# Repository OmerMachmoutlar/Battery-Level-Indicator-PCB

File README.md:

# 12V Akü Seviye Göstergesi Tasarımı (PCB Projesi)

Bu proje, harici bir voltaj kaynağını (12V Akü) izlemek için tasarlanmış, baştan sona (tasarım-üretim-montaj) tarafımdan gerçekleştirilmiş bir PCB projesidir.

## Proje Amacı
Akü voltaj seviyesini görsel olarak (LED'ler vb. ile) kullanıcıya bildiren kompakt bir elektronik devre kartı üretmek.

## Kullanılan Teknolojiler ve Süreçler
* **PCB Tasarımı:** Autodesk Eagle (Şematik ve Board çizimi)
* **Üretim Yöntemi:** CNC Kazıma (CNC Milling)
* **Montaj:** Through-hole bileşenlerin manuel lehimlenmesi (Soldering)

## Dosya İçeriği
* Eagle devre şeması.
* PCB yerleşim planı (Layout).
* CNC ile üretilip lehimlenmiş kartın fotoğrafı.

## Kazanımlar
Bu proje ile PCB tasarım kuralları, yol genişlikleri (trace width), CNC ile prototip üretim ve lehimleme teknikleri konusunda pratik deneyim kazanılmıştır.

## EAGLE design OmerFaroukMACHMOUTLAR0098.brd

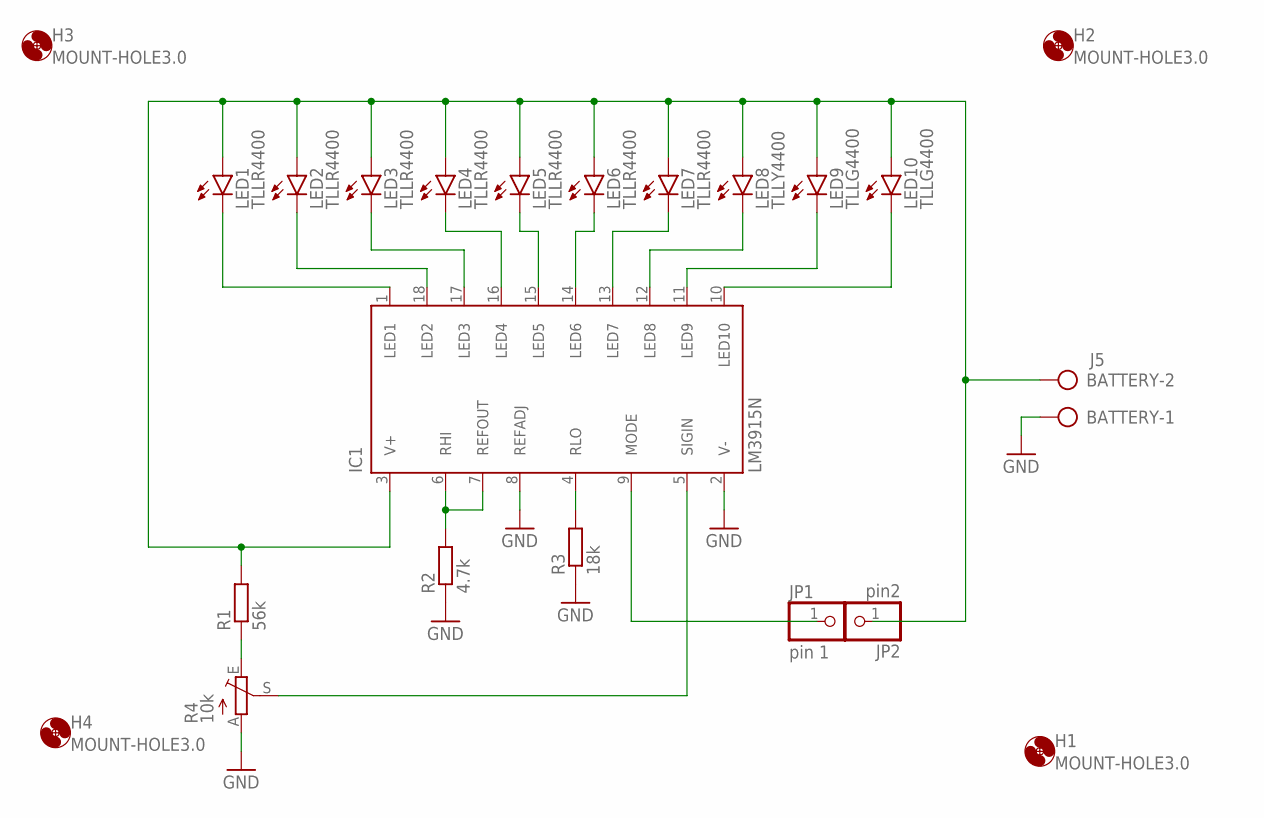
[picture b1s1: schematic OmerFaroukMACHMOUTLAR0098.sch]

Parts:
BATTERY: J5; AK500/2
H1, H2, H3, H4: MOUNT-HOLE3.0; 3,0
IC1: LM3915N; DIL18
JP1: pin 1; 1X01
JP2: pin2; 1X01
LED1, LED2, LED3, LED4, LED5, LED6, LED7: TLLR4400; LED3MM
LED8: TLLY4400; LED3MM
LED9, LED10: TLLG4400; LED3MM
R1: 56k; 0204/7
R2: 4.7k; 0204/7
R3: 18k; 0204/7
R4: 10k; S64W

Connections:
GND: BATTERY.1, IC1.2 (V-), IC1.8 (REFADJ), R2.1, R3.1, R4.A
unnamed: IC1.15 (LED5), LED5.K (C)
unnamed: IC1.14 (LED6), LED6.K (C)
unnamed: IC1.16 (LED4), LED4.K (C)
unnamed: IC1.13 (LED7), LED7.K (C)
unnamed: IC1.17 (LED3), LED3.K (C)
unnamed: IC1.1 (LED1), LED1.K (C)
unnamed: IC1.12 (LED8), LED8.K (C)
unnamed: IC1.18 (LED2), LED2.K (C)
unnamed: IC1.11 (LED9), LED9.K (C)
unnamed: IC1.10 (LED10), LED10.K (C)
unnamed: IC1.6 (RHI), IC1.7 (REFOUT), R2.2
unnamed: IC1.4 (RLO), R3.2
unnamed: BATTERY.2, IC1.3 (V+), JP2.1, LED1.A, LED2.A, LED3.A, LED4.A, LED5.A, LED6.A, LED7.A, LED8.A, LED9.A, LED10.A, R1.2
unnamed: IC1.9 (MODE), JP1.1
unnamed: IC1.5 (SIGIN), R4.S
unnamed: R1.1, R4.E

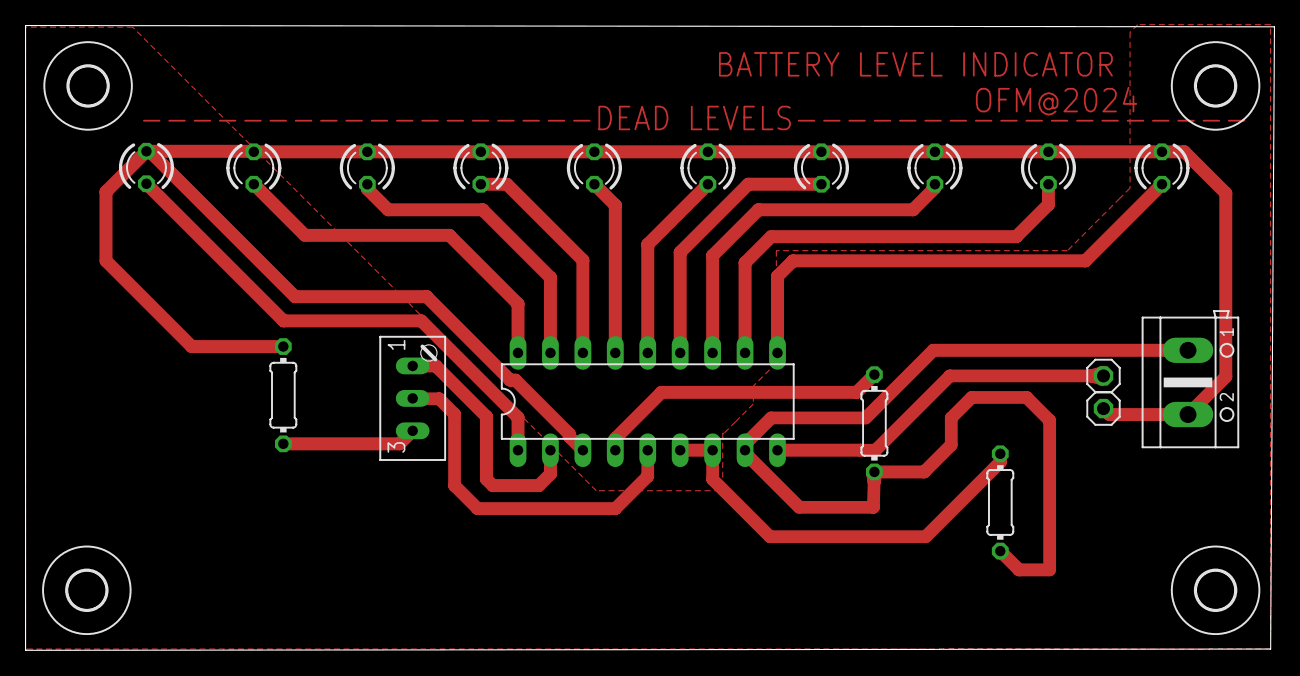
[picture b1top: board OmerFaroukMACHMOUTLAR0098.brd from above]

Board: 2 copper layers, 97.8 x 48.9 mm, 22 parts (0 on the bottom side), 17 nets.

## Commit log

2026-02-04 README.md
